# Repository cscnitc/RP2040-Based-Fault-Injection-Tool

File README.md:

# RP2040 Voltage Fault Injection Tool

A PicoGlitcher based hardware platform for voltage fault-injection experiments, using Raspberry Pi Pico PIO state machines for timing without an FPGA. The board combines MOSFET crowbar glitching, selectable supply-voltage multiplexing, and software-controlled target power routing on a shared target supply output.

The initial target is the **MSP-LITO-L2228 board based on the TI MSPM0L2228**, for eCTF experiments.

## Project status

The schematic and a four-layer PCB layout have been developed. The current timing goal is approximately **200–300 ns crowbar command pulses**. This is a design goal for the control signal; the resulting voltage dip at the target MCU has not yet been recorded.

Neither the Firmware or the PCB has been implemented yet.

## Features

- RP2040-based experiment control and PIO pulse sequencing.
- Two selectable crowbar paths: direct and through a 0.1 Ω source resistor.
- A dedicated dual-channel MOSFET gate driver powered from 12 V.
- Voltage selection using 3.3 V, 1.8 V, or an external user voltage.
- Independently controlled normal-supply and multiplexed-supply paths.
- A shared `VDD_VICTIM` connection for the external target.
- Three trigger input

The target supply is the common node between the selected power source, the crowbar devices, and the voltage-monitoring circuit. The controller has its own supply, allowing it to remain active while the target voltage is disturbed.

## 1. Controller and timing

The Raspberry Pi Pico provides the RP2040 controller. Its responsibilities are to configure the operating mode, select a voltage source, arm a trigger, sequence the glitch outputs, and monitor target supply voltage.

PIO state machines are intended to handle timing-critical operations.

Gate-driver propagation, MOSFET switching, target capacitance, and connection inductance determine the actual supply waveform. Trigger sampling also contributes latency; the completed firmware must account for its configuration.

## 2. Crowbar stage

The crowbar stage briefly creates a low-resistance path from `VDD_VICTIM` to ground. It discharges energy stored in the target supply capacitance and disturbs the MCU's operating voltage.

Two **IRF7832PBF N-channel MOSFETs** provide different discharge paths:

One directly shorts the power rail to Ground

The other shorts the power rail to ground through a 0.1 ohm source resistart for alternative discharge characteristic

The 0.1 Ω resistor does not establish a fixed peak-current limit. 

The design intentionally has no active current-limiting stage in these crowbar branches.

### Gate drive

**U2, a UCC27524D dual gate driver**, is supplied from the 12 V rail. I

Both driver inputs are connected to the same `INA` net. `ENA` and `ENB` select which channels respond to that input. 

## 3. Voltage multiplexing

**U4, a TS3A4751PWR**, contains four independently controlled analog switches. Their output terminals are tied together at `MUX_OUT`, creating a selectable voltage source.

| Control net | Source connected to MUX_OUT |
|---|---|
| `MIN1` | `3V3M`, the dedicated 3.3 V MUX supply |
| `MIN2` | `USER_COM`, an external user-supplied voltage |
| `MIN3` | `1V8`, the dedicated 1.8 V supply |
| `MIN4` | Ground |

Channel selection is implemented in firmware rather than through an external decoder and inverter stage.

Only one source should be selected at a time. Changes between sources therefore require an all-off transition.

Although the schematic includes a ground channel, the intended operation excludes passing a zero-volt MUX source through the TPS22918 path. Ground selection is not presented as a validated end-to-end operating mode.

`USER_COM` is an analog voltage source for the MUX, not a Pico GPIO input. Its voltage must remain within the analog switch's permitted range. The target's approximately 5 mA measured.

## 4. Target power routing

The board routes two supply paths to the same target output:

```text
AMS1117 3.3 V ── J6 link ── 3V3C ── Load Switch ────|
                                                    ├── VDD_VICTIM ── target
Selected voltage ── MUX_OUT ── Load Switch ─────────|
```

- **U8** connects the normal `3V3C` source under `CROW_LD` control.
- **U7 and U9** form a common-output, back-to-back pair between `MUX_OUT` and the target, under `MUX_LD` control.
- **J6** provides a link between U1's output and the `3V3C` supply net.

The TPS22918 switches select or disconnect the supply paths between experiments or operating modes. They are not the components intended to generate the 200–300 ns crowbar pulse.

The back-to-back MUX arrangement is intended to address reverse conduction through that branch. U8 is a single load switch, so the overall board should not be treated as providing complete bidirectional isolation on every supply path. 

Firmware is responsible for preventing unintended source overlap and returning the outputs to a defined state after each experiment. There is no dedicated hardware interlock enforcing the complete operating sequence.

## 7. Trigger

Three external trigger connections, `TRIG`, `TRIG1`, and `TRIG2`, connect to Pico GPIOs with pull-down resistors. They allow firmware to select trigger sources for an experiment. These are direct logic interfaces with no level translation shown in the reviewed schematic.

## 8. RP2040 pin mapping

GPIO numbers below are RP2040 GPIO identifiers, not Pico physical pin numbers.

| GPIO | Net | Function |
|---|---|---|
| GPIO3 | `TRIG` | Trigger input |
| GPIO4 | `TRIG1` | Trigger input |
| GPIO5 | `TRIG2` | Trigger input |
| GPIO8 | `MIN2` | Select USER_COM |
| GPIO9 | `MIN3` | Select 1.8 V |
| GPIO10 | `MIN4` | Select ground channel |
| GPIO11 | `MIN1` | Select MUX 3.3 V |
| GPIO12 | `CROW_LD` | Control normal-supply switch U8 |
| GPIO16 | `INA` | Shared gate-driver pulse input |
| GPIO17 | `ENA` | Enable channel A / IC1 |
| GPIO18 | `ENB` | Enable channel B / IC2 |
| GPIO22 | `MUX_LD` | Control U7 / U9 MUX supply path |
| GPIO26 / ADC0 | `VDD_ADC` | Filtered target-voltage measurement |

## 9. External connectors

| Connector | Signals | Role |
|---|---|---|
| J1 | `+12V`, GND | External board supply |
| J2 | `VDD_VICTIM`, GND | Target supply and fault connection |
| J3 | `TRIG`, GND | Trigger input |
| J4 | `TRIG1`, GND | Trigger input |
| J5 | `TRIG2`, GND | Trigger input |
| J6 | U1 output, `3V3C` | Normal target-supply link |
| J7 | `USER_COM`, GND | External MUX voltage input |

## 10. PCB architecture

The four-layer layout approach uses:

| Layer | Intended role |
|---|---|
| L1 | Components, short signal routes, power and ground copper |
| L2 | Continuous ground reference plane |
| L3 | Signal routing and power distribution where needed |
| L4 | Additional routing and power/ground copper |

The copper-weight target is 2 oz on the outer layers and 1 oz on the inner layers.

## Validation still to document

- Regulator stability and settling with each supply path selected.
- Startup, mode transitions, and source-disconnect behavior.
- Gate-to-source waveforms on both crowbar devices.
- Target-rail dip depth, duration, ringing, and recovery measured at the MCU.
- Peak-current and repetition-rate limits for the assembled circuit.
- Trigger-to-pulse timing and complete PIO firmware behavior.

This project is inspired by [PicoGlitcher and the Fault Injection Library](https://github.com/MKesenheimer/fault-injection-library). It explores a custom combination of crowbar and voltage-multiplexing paths with a shared target connection and direct GPIO control of the analog switches.

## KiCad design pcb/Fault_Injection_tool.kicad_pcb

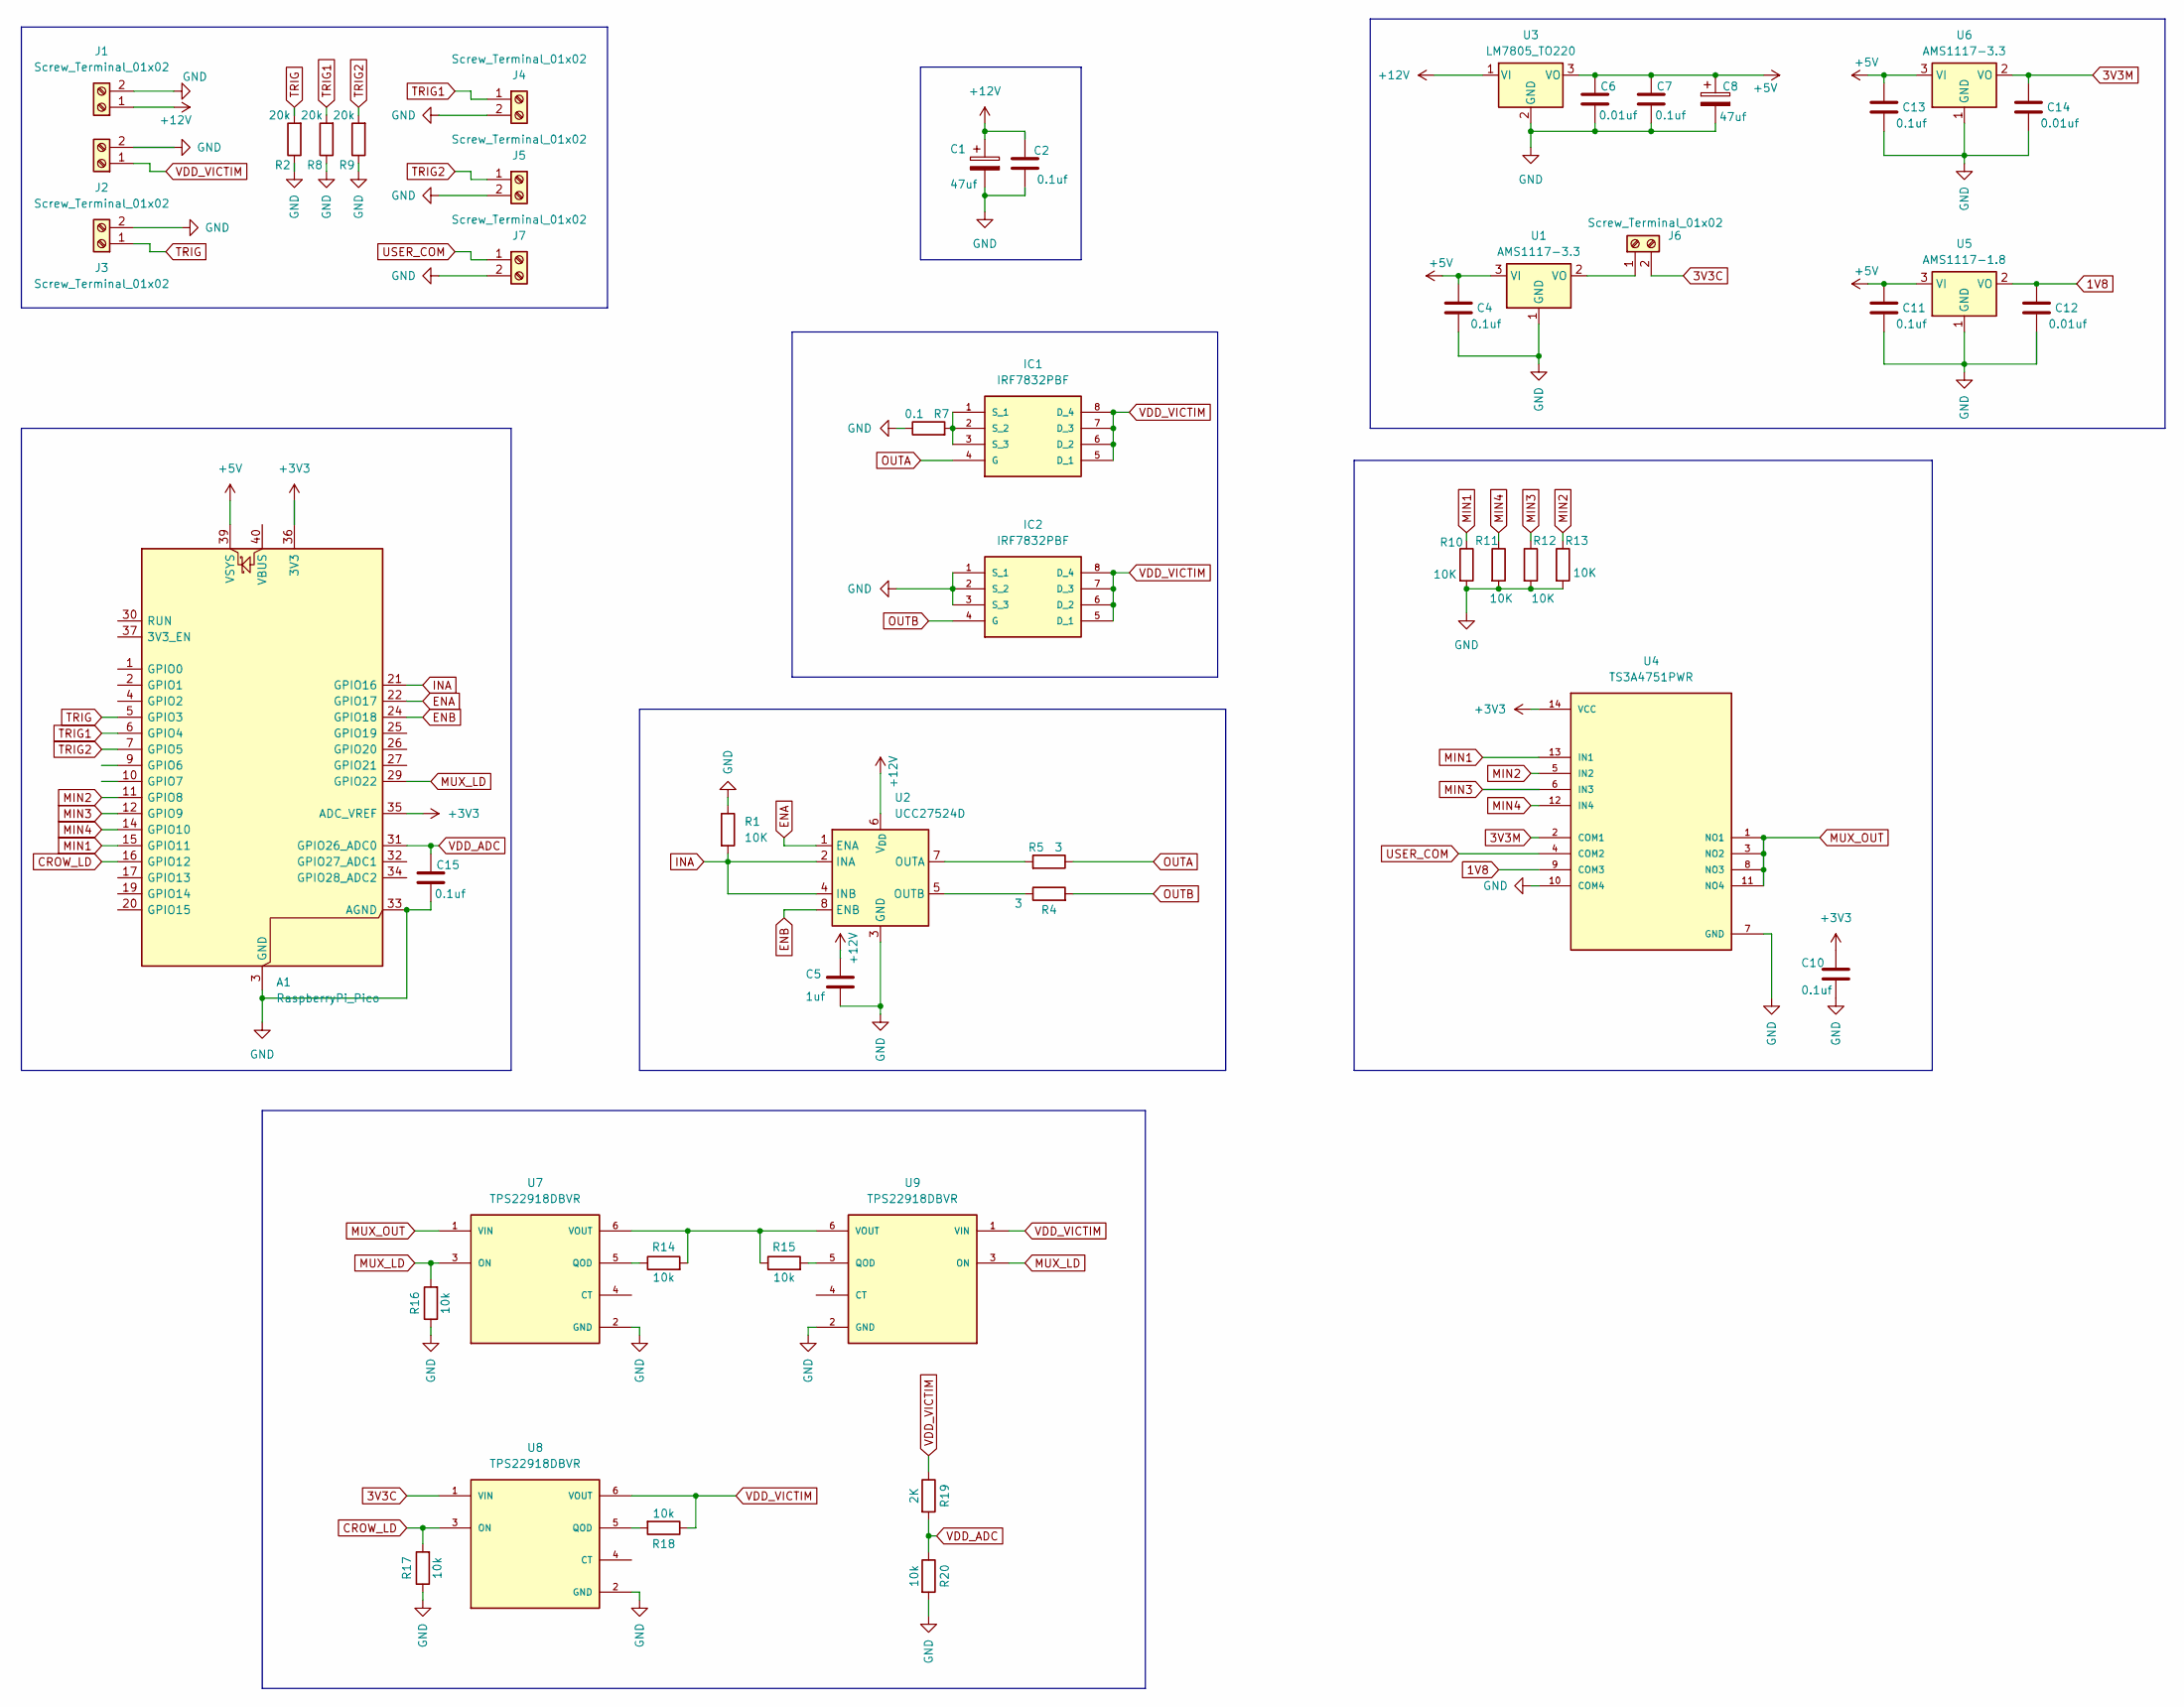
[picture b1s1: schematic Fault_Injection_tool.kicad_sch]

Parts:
A1: RaspberryPi_Pico; RaspberryPi_Pico_Common_THT
C1, C8: 47uf; C_Radial_D4.0mm_H7.0mm_P1.50mm
C2, C4, C7, C10, C11, C13, C15: 0.1uf; C_0805_2012Metric_Pad1.18x1.45mm_HandSolder
C5: 1uf; C_0805_2012Metric_Pad1.18x1.45mm_HandSolder
C6, C12, C14: 0.01uf; C_0805_2012Metric_Pad1.18x1.45mm_HandSolder
IC1, IC2: IRF7832PBF; SOIC127P600X175-8N; MOUSER_PART_NUMBER 942-IRF7832PBF
J1, J6, J7: Screw_Terminal_01x02; TerminalBlock_Xinya_XY308-2.54-2P_1x02_P2.54mm_Horizontal
J2, J3, J4, J5: Screw_Terminal_01x02; PinHeader_1x02_P2.54mm_Vertical
R1, R10, R11, R12, R13: 10K; R_0805_2012Metric_Pad1.20x1.40mm_HandSolder
R2, R8, R9: 20k; R_0805_2012Metric_Pad1.20x1.40mm_HandSolder
R4, R5: 3; R_0805_2012Metric_Pad1.20x1.40mm_HandSolder
R7: 0.1; R_Axial_DIN0411_L9.9mm_D3.6mm_P12.70mm_Horizontal
R14, R15, R16, R17, R18, R20: 10k; R_0805_2012Metric_Pad1.20x1.40mm_HandSolder
R19: 2K; R_0805_2012Metric_Pad1.20x1.40mm_HandSolder
U1, U6: AMS1117-3.3; SOT-223-3_TabPin2
U2: UCC27524D; SOIC-8_3.9x4.9mm_P1.27mm
U3: LM7805_TO220; TO-220-3_Vertical
U4: TS3A4751PWR; SOP65P640X120-14N; PARTREV F
U5: AMS1117-1.8; SOT-223-3_TabPin2
U7, U8, U9: TPS22918DBVR; SOT95P280X145-6N; PARTREV C

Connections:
1V8: C12.1, U4.9 (COM3), U5.2 (VO)
3V3C: J6.2, U8.1 (VIN)
3V3M: C14.1, U4.2 (COM1), U6.2 (VO)
+3V3: A1.35 (ADC_VREF), A1.36 (3V3), C10.1, U4.14 (VCC)
+5V: A1.39 (VSYS), C4.1, C6.1, C7.1, C8.1, C11.1, C13.1, U1.3 (VI), U3.3 (VO), U5.3 (VI), U6.3 (VI)
+12V: C1.1, C2.1, C5.1, J1.1, U2.6 (V_{DD}), U3.1 (VI)
CROW_LD: A1.16 (GPIO12), R17.2, U8.3 (ON)
ENA: A1.22 (GPIO17), U2.1 (ENA)
ENB: A1.24 (GPIO18), U2.8 (ENB)
GND: A1.3 (GND), A1.8 (GND), A1.13 (GND), A1.18 (GND), A1.23 (GND), A1.28 (GND), A1.33 (AGND), A1.38 (GND), C1.2, C2.2, C4.2, C5.2, C6.2, C7.2, C8.2, C10.2, C11.2, C12.2, C13.2, C14.2, C15.2, IC2.1 (S_1), IC2.2 (S_2), IC2.3 (S_3), J1.2, J2.2, J3.2, J4.2, J5.2, J7.2, R1.1, R2.1, R7.1, R8.1, R9.1, R10.2, R11.2, R12.2, R13.2, R16.1, R17.1, R20.2, U1.1 (GND), U2.3 (GND), U3.2 (GND), U4.7 (GND), U4.10 (COM4), U5.1 (GND), U6.1 (GND), U7.2 (GND), U8.2 (GND), U9.2 (GND)
INA: A1.21 (GPIO16), R1.2, U2.2 (INA), U2.4 (INB)
MIN1: A1.15 (GPIO11), R10.1, U4.13 (IN1)
MIN2: A1.11 (GPIO8), R13.1, U4.5 (IN2)
MIN3: A1.12 (GPIO9), R12.1, U4.6 (IN3)
MIN4: A1.14 (GPIO10), R11.1, U4.12 (IN4)
MUX_LD: A1.29 (GPIO22), R16.2, U7.3 (ON), U9.3 (ON)
MUX_OUT: U4.1 (NO1), U4.3 (NO2), U4.8 (NO3), U4.11 (NO4), U7.1 (VIN)
unnamed: IC1.1 (S_1), IC1.2 (S_2), IC1.3 (S_3), R7.2
unnamed: J6.1, U1.2 (VO)
unnamed: R5.2, U2.7 (OUTA)
unnamed: R4.1, U2.5 (OUTB)
unnamed: R14.1, U7.5 (QOD)
unnamed: R14.2, R15.1, U7.6 (VOUT), U9.6 (VOUT)
unnamed: R18.2, U8.5 (QOD)
unnamed: R15.2, U9.5 (QOD)
OUTA: IC1.4 (G), R5.1
OUTB: IC2.4 (G), R4.2
TRIG: A1.5 (GPIO3), J3.1, R2.2
TRIG1: A1.6 (GPIO4), J4.1, R8.2
TRIG2: A1.7 (GPIO5), J5.1, R9.2
USER_COM: J7.1, U4.4 (COM2)
VDD_ADC: A1.31 (GPIO26_ADC0), C15.1, R19.2, R20.1
VDD_VICTIM: IC1.5 (D_1), IC1.6 (D_2), IC1.7 (D_3), IC1.8 (D_4), IC2.5 (D_1), IC2.6 (D_2), IC2.7 (D_3), IC2.8 (D_4), J2.1, R18.1, R19.1, U8.6 (VOUT), U9.1 (VIN)

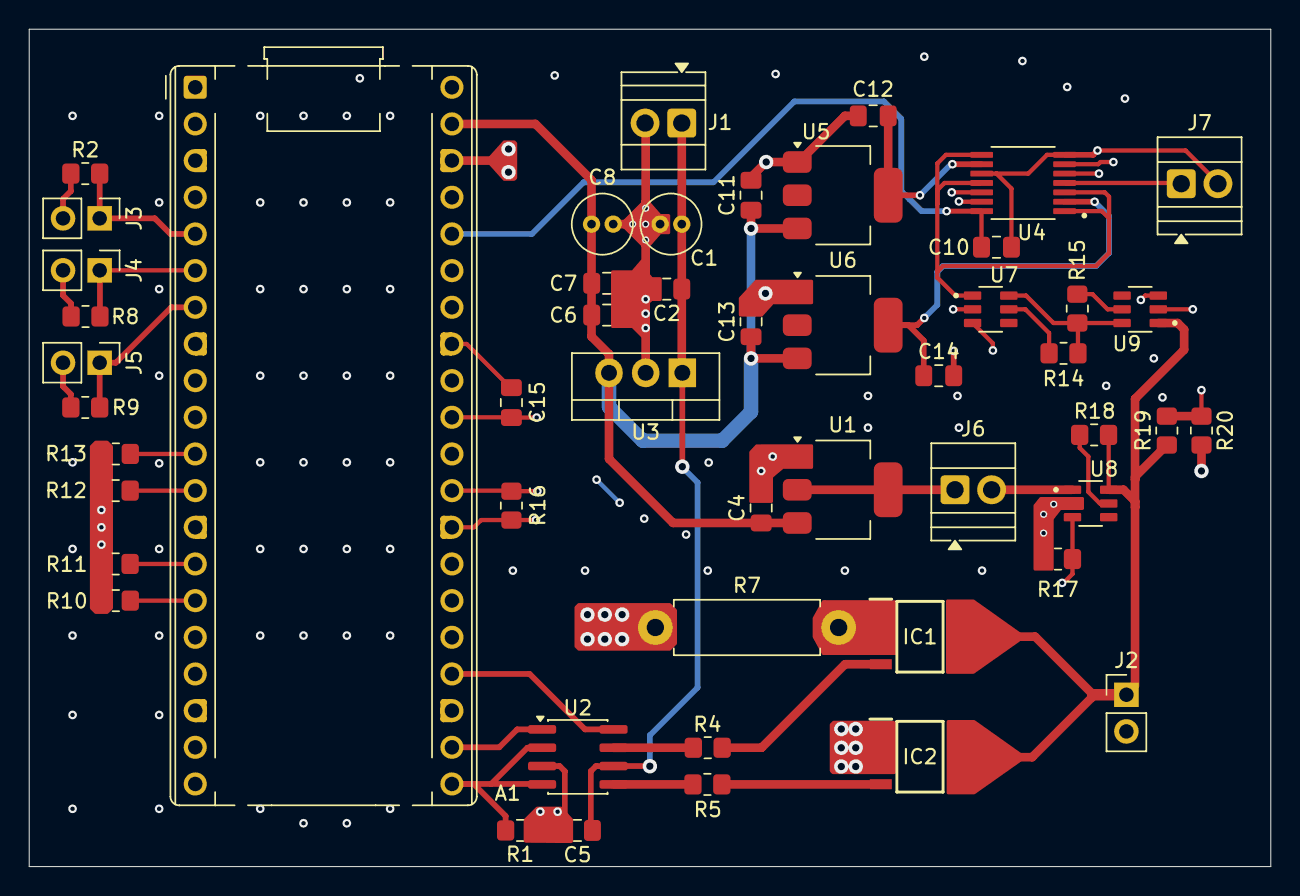
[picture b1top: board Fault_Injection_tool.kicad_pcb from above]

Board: 4 copper layers, 86.0 x 58.0 mm, 50 parts (0 on the bottom side), 33 nets.
